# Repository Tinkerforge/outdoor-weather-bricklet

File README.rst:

Outdoor Weather Bricklet
========================

This repository contains the firmware source code and the hardware design
files. The documentation generator configs can be found at
https://github.com/Tinkerforge/generators

Repository Content
------------------

software/:
 * examples/: Examples for all supported languages
 * build/: Compiled files
 * src/: Source code of firmware
 * Makefile: Makefile to build project

hardware/:
 * Contains KiCad project files and additionally schematics as PDF

datasheets/:
 * Contains datasheets for sensors and complex ICs that are used

Hardware
--------

The hardware is designed with the open source EDA Suite KiCad
(http://www.kicad.org). Before you are able to open the files,
you have to install the Tinkerforge kicad-libraries
(https://github.com/Tinkerforge/kicad-libraries). You can either clone
them directly in hardware/ or clone them in a separate folder and
symlink them into hardware/
(ln -s kicad_path/kicad-libraries project_path/hardware). After that you
can open the .pro file in hardware/ with KiCad and from there view and
modify the schematics and the PCB layout.

Software
--------

If you want to do your own Brick/Bricklet firmware development we highly
recommend that you use our build environment setup script and read the
tutorial (https://www.tinkerforge.com/en/doc/Tutorials/Tutorial_Build_Environment/Tutorial.html).

To compile the C code we recommend you to install the newest GNU Arm Embedded
Toolchain (https://launchpad.net/gcc-arm-embedded/+download).
You also need to install bricklib2 (https://github.com/Tinkerforge/bricklib2).

You can either clone it directly in software/src/ or clone it in a
separate folder and symlink it into software/src/
(ln -s bricklib_path/bricklib2 project_path/software/src/). Finally make sure to
have CMake installed (http://www.cmake.org/cmake/resources/software.html).

After that you can build the firmware by invoking make in software/.
The firmware (.zbin) can then be found in software/build/ and uploaded
with brickv (click button "Flashing" on start screen).

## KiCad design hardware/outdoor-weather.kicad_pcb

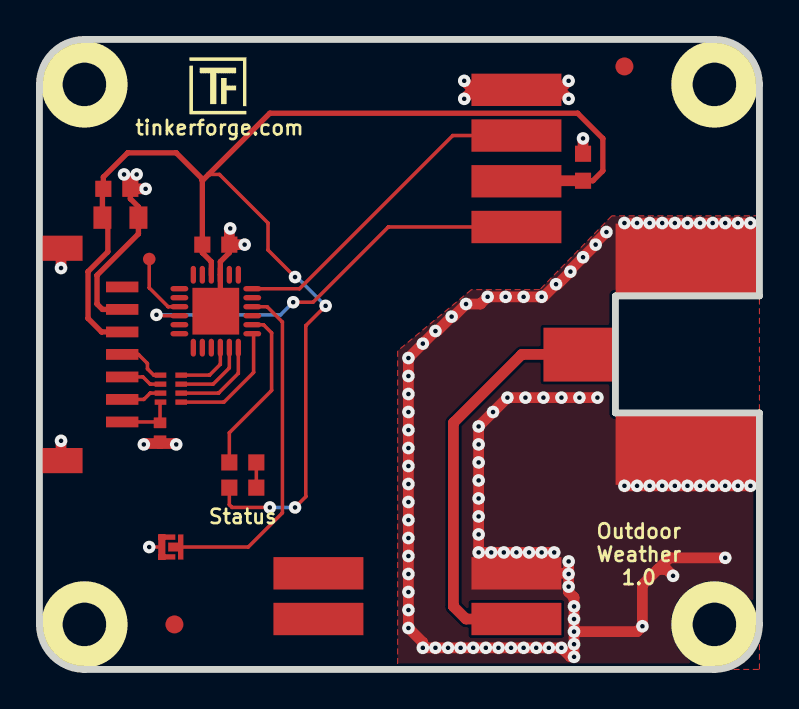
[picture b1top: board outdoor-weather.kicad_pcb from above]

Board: 2 copper layers, 40.0 x 35.0 mm, 22 parts (0 on the bottom side), 17 nets.

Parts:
ANT1: FT-004B
C1: 220pF; C0402F
C2: 10uF; C0805
C3: 1uF; C0603F
C4, C5: 100nF; C0603F
D1: blue; D0603F
Fiducial_Mark: VAL**; Fiducial_Mark
Fiducial_Mark#2: VAL**; Fiducial_Mark
J1: Debug; DEBUG_PAD
P1: CON-SENSOR2
P2: Boot; SolderJumper
R1: 1k; R0603F
RP1: 82; 4X0402
U1: XMC110024; QFN24-4x4mm-0.5mm
U2: RFM210LCF-S1
U4, U5, U6, U7: DRILL; DRILL_NP
VAL: CE_5mm
VAL#2: WEEE_7mm

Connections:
DATA: U1.6, U2.5
GND: ANT1.2, C1.1, C2.1, C3.1, C4.1, C5.1, P1.2, P1.EP, P2.1, U1.9, U1.EXP, U2.2, U2.6
unnamed: ANT1.1, U2.1
unnamed: C1.2, P1.7, RP1.4
unnamed: D1.2, R1.2
unnamed: J1.1, U1.15
unnamed: P1.4, RP1.1
unnamed: P1.5, RP1.2
unnamed: P1.6, RP1.3
unnamed: P2.2, U1.4
unnamed: R1.1, U1.2
S-CLK: RP1.7, U1.23
S-CS: RP1.8, U1.22
S-MISO: RP1.5, U1.1
S-MOSI: RP1.6, U1.24
SDN: U1.16, U2.3
VCC: C2.2, C3.2, C4.2, C5.2, D1.1, P1.3, U1.10, U2.4

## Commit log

2017-08-30 Initial commit
    At this point data is already received properly from weather station
    and printed with uartbb output
2017-08-30 Add .gitignore
2017-08-30 Add datasheets
2017-08-30 Add simple tests
2017-08-30 Save data for all 256 weather station device ids
2017-08-30 Add API implementation
2017-08-30 Change wind/gust speed and rain resolution
2017-09-06 hardware files for outdoor weather bricklet, pcb only copy of motion detector
2017-09-08 briklet finished
2017-09-08 remove silkscreen layers from footprints
2017-09-28 Switch MCU from 1400 to 1100
2017-09-29 add status led text
2017-10-26 specify processor type
2017-11-03 Add support for simultaneous station/sensor usage
2018-02-02 Add initial set of examples
2018-02-02 examples: Reorder callbacks
2018-02-05 Add 3d information (final)
2018-02-05 Add 3d model (*.step & *.FCStd)
2018-02-16 Minor optical adjustments
2018-02-16 Add schematic (PDF)
2018-02-19 Add WS-6147 datasheet
2018-02-19 Disable debug
2018-02-19 javascript: Close div tag correctly
2018-02-20 Cleanup KiCad libraries config
    Ensure LibDir=kicad-libraries and LibName1=tinkerforge.
    Remove special library.
2018-02-28 Neues Foto Bricklet mit Master eingefügt
2018-02-28 Add new 3d model with more detailed components
2018-03-02 Fix outline from antenna connector larger caused thru production tolerance
2018-03-05 Remove unused flash-size define
2018-04-13 Beschreibung korrigiert
2018-05-11 Rename files
2018-05-24 perl: Use strict in examples
2018-06-18 Change capacitor footprint(s) to C0402F
2018-06-28 Fix readme
2018-07-06 Add LabVIEW examples
2018-07-11 Add Makefile with docker support
2018-07-11 Update directory structure and build instructions
2018-07-11 Remove obsolete generate_makefile scripts
2018-10-04 Increase version for new release (changes in bricklib2)
2018-10-04 Add rev to changelog
2018-11-06 Add rust examples
2018-11-07 rust: Accept host names for ip connection, fix naming inconsistencies
2018-11-07 rust: Rename callback receivers.
2018-12-14 Add go examples.
2018-12-14 go: Fix printf parameters.
2018-12-18 go: Change import path.
2018-12-18 go: Change import path again.
2018-12-20 Fix constant handling in examples.
2018-12-20 rust: Reformat examples.
2019-01-24 mqtt: Add examples.
2019-01-24 mqtt: Fix example header.
2019-01-24 mqtt: Remove executable bit in example permissions.
2019-01-24 go: Minor example fixes.
2019-01-24 mqtt: Minor example fixes.
2019-02-05 Remove Station/Sensor from list of identifiers after 12h with no data
2019-05-22 Add changelog commit refs
2019-05-29 Disallow SPITFP interrupt to disable IRQs
    The newest version of bricklib2 disables IRQs during SPITFP
    transfers by default. This needs to be turned off for this
    Bricklet since it has higher priority IRQs that can not wait.
    For this we set the SPITFP_NOT_ALLOWED_TO_DISABLE_IRQ define.
2019-06-06 Increase minimum gap between messages to filter duplicates.
2019-06-06 Add commit ref to changelog.
2019-06-06 Update changelog
2019-08-22 c: Adapt to bindings changes
2019-08-27 go: Escape '%' in examples.
2020-01-13 examples: Use python3 input instead of python2 raw_input.
2020-01-13 examples: mqtt: Remove trailing whitespace.
2020-03-16 Whitespace
2020-04-07 examples: rust: Always block when calling bindings functions.
2020-08-19 Add uc examples.
2020-08-25 uc: Fix whitespace
2020-08-27 uc: Fix warnings.
2020-08-31 uc: Use fixed-with placeholders in format strings.
2020-09-02 uc: Add example driver note.
2020-10-16 uc: Fix divisor type.
2021-10-25 Update KiCad link
    https://www.kicad.org/blog/2021/10/Avoid-links-to-former-kicad-domain/
2022-04-19 examples: uc: Rename TF_HalContext to TF_HAL.
2022-04-27 uc: Adapt to bindings changes
2022-07-06 Add license files.
2025-10-04 Fix compatibility with new Docker build image (GCC 14.2.1)

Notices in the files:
hardware/outdoor-weather.kicad_pcb:
Licensed under CERN OHL v.1.1
Copyright (©) 2017, B.Nordmeyer
Copyright Tinkerforge GmbH 2017.
This documentation describes Open Hardware and is licensed under the
CERN OHL v. 1.1.
